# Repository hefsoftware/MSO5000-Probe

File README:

MSO5000 digital probe. 

The schematic was taken almost verbatim from Faeton's digital-probe-rigol-mso5000 (https://oshwlab.com/f33net/digital-probe-rigol-mso5000).
As their work is acknowledged in the original work a special thank goes to people from EEVblog for pinout of the connector.

Changes from Faeton's:
The schematic and PCB were drawn with Kicad.
The single LVDS buffer SN65LVDS1 was replaced with a 4-line buffer SN65LVDS04. 
Changed linear regulator to MCP1825ST-3302E/DB which has a different pinout from original (available on Digikey)
Inputs order was switched from original (now pin 0 is on the left and pin 15 is on the right) to make routing more "natural" and make the board more compact.

TODO: Add option for switching tab from GND to Vin to make use of original regulator MC33375ST-3.3T3G.

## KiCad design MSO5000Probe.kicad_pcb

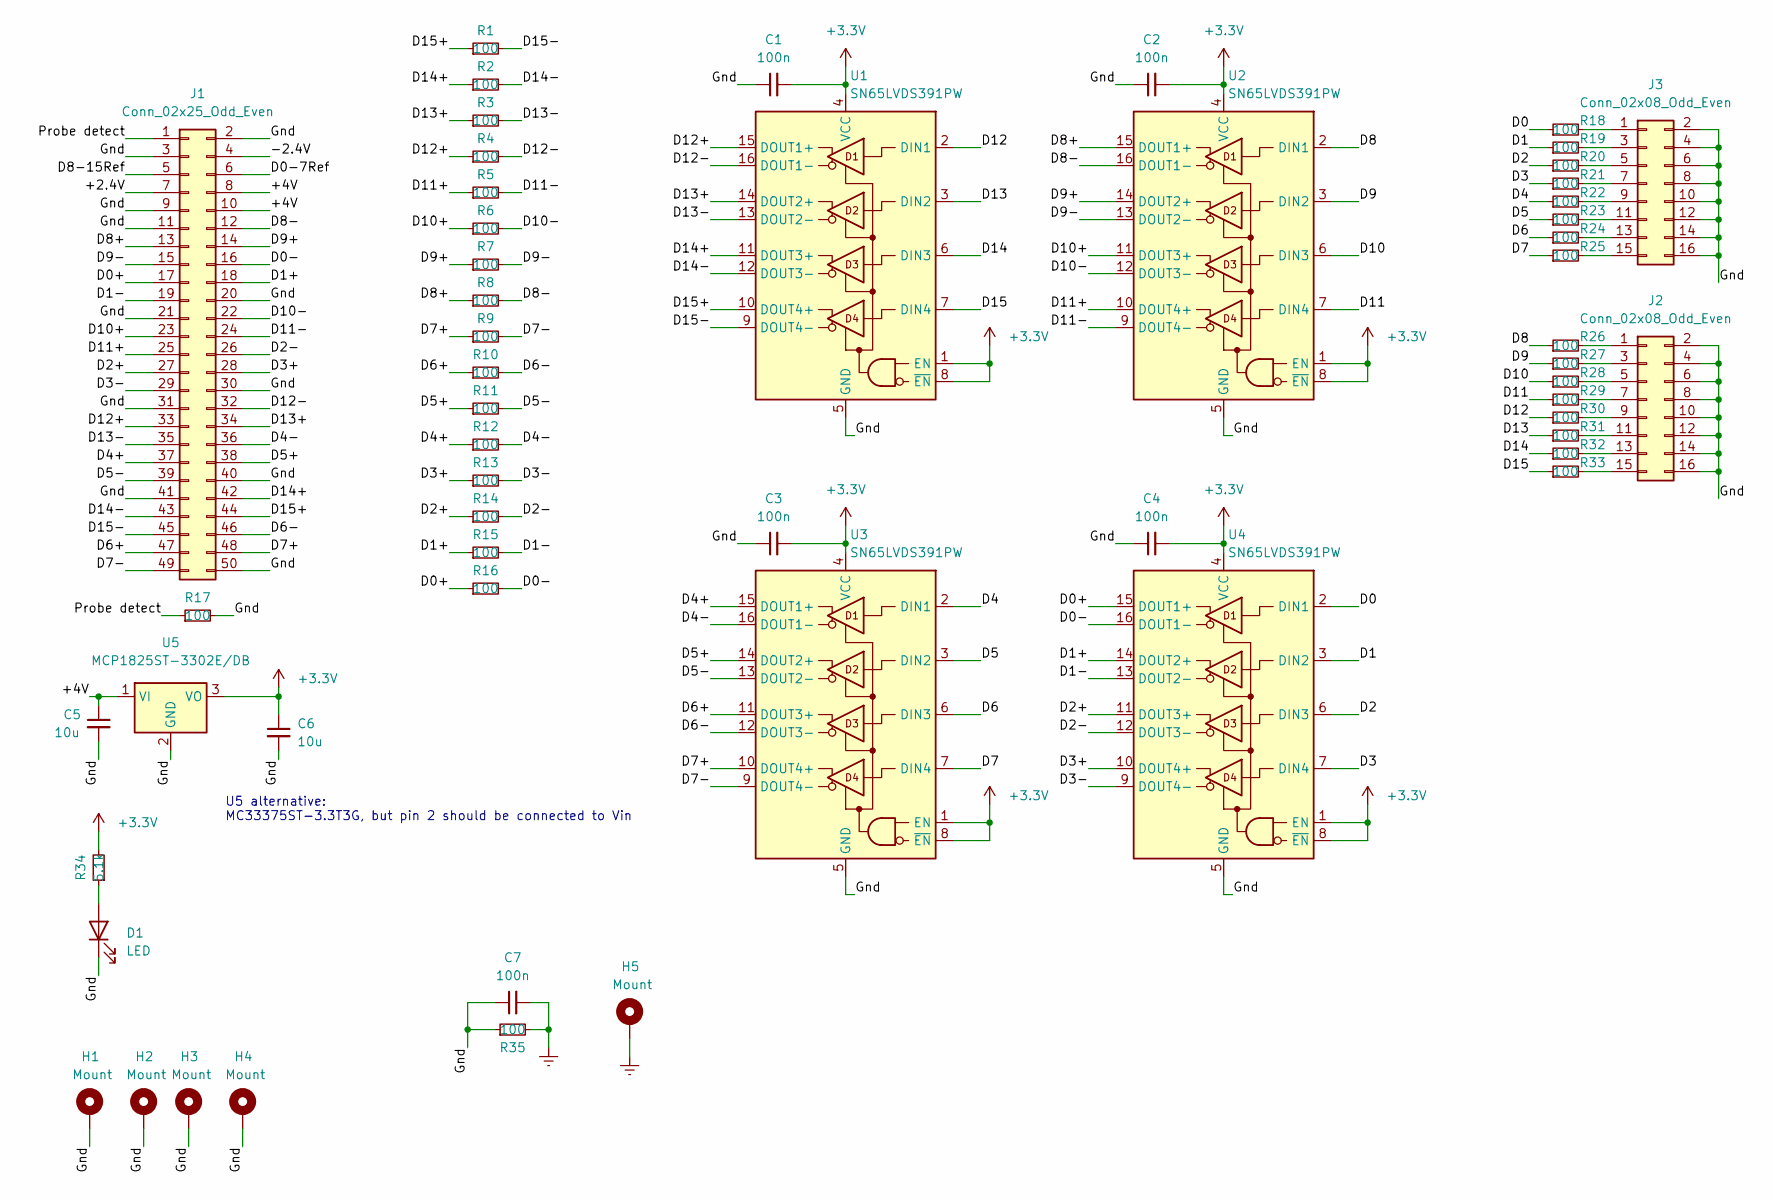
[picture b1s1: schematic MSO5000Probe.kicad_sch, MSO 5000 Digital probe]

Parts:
C1, C2, C3, C4, C7: 100n; C_0805_2012Metric_Pad1.18x1.45mm_HandSolder
C5, C6: 10u; C_0805_2012Metric_Pad1.18x1.45mm_HandSolder
D1: LED; LED_1206_3216Metric_Pad1.42x1.75mm_HandSolder
H1, H2, H3, H4: Mount; MountingHole_2.7mm_Pad_Via
H5: Mount; TestPoint_THTPad_2.5x2.5mm_Drill1.2mm
J1: Conn_02x25_Odd_Even; IDC-Header_2x25_P2.54mm_Vertical
J2, J3: Conn_02x08_Odd_Even; IDC-Header_2x08_P2.54mm_Horizontal
R1, R2, R3, R4, R5, R6, R7, R8, R9, R10, R11, R12, R13, R14, R15, R16, R17, R18, R19, R20, R21, R22, R23, R24, R25, R26, R27, R28, R29, R30, R31, R32, R33, R35: 100; R_0805_2012Metric_Pad1.20x1.40mm_HandSolder
R34: 5.1k; R_0805_2012Metric_Pad1.20x1.40mm_HandSolder
U1, U2, U3, U4: SN65LVDS391PW; TSSOP-16_4.4x5mm_P0.65mm
U5: MCP1825ST-3302E/DB; SOT-223-3_TabPin2

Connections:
+3V3: C1.2, C2.2, C3.2, C4.2, C6.1, R34.2, U1.1 (EN), U1.4 (VCC), U1.8 (~EN), U2.1 (EN), U2.4 (VCC), U2.8 (~EN), U3.1 (EN), U3.4 (VCC), U3.8 (~EN), U4.1 (EN), U4.4 (VCC), U4.8 (~EN), U5.3 (VO)
/+2.4V: J1.7
/+4V: C5.1, J1.8, J1.10, U5.1 (VI)
/-2.4V: J1.4
/D0: R18.1, U4.2 (DIN1)
/D0+: J1.17, R16.1, U4.15 (DOUT1+)
/D0-: J1.16, R16.2, U4.16 (DOUT1-)
/D0-7Ref: J1.6
/D1: R19.1, U4.3 (DIN2)
/D1+: J1.18, R15.1, U4.14 (DOUT2+)
/D1-: J1.19, R15.2, U4.13 (DOUT2-)
/D2: R20.1, U4.6 (DIN3)
/D2+: J1.27, R14.1, U4.11 (DOUT3+)
/D2-: J1.26, R14.2, U4.12 (DOUT3-)
/D3: R21.1, U4.7 (DIN4)
/D3+: J1.28, R13.1, U4.10 (DOUT4+)
/D3-: J1.29, R13.2, U4.9 (DOUT4-)
/D4: R22.1, U3.2 (DIN1)
/D4+: J1.37, R12.1, U3.15 (DOUT1+)
/D4-: J1.36, R12.2, U3.16 (DOUT1-)
/D5: R23.1, U3.3 (DIN2)
/D5+: J1.38, R11.1, U3.14 (DOUT2+)
/D5-: J1.39, R11.2, U3.13 (DOUT2-)
/D6: R24.1, U3.6 (DIN3)
/D6+: J1.47, R10.1, U3.11 (DOUT3+)
/D6-: J1.46, R10.2, U3.12 (DOUT3-)
/D7: R25.1, U3.7 (DIN4)
/D7+: J1.48, R9.1, U3.10 (DOUT4+)
/D7-: J1.49, R9.2, U3.9 (DOUT4-)
/D8: R26.1, U2.2 (DIN1)
/D8+: J1.13, R8.1, U2.15 (DOUT1+)
/D8-: J1.12, R8.2, U2.16 (DOUT1-)
/D8-15Ref: J1.5
/D9: R27.1, U2.3 (DIN2)
/D9+: J1.14, R7.1, U2.14 (DOUT2+)
/D9-: J1.15, R7.2, U2.13 (DOUT2-)
/D10: R28.1, U2.6 (DIN3)
/D10+: J1.23, R6.1, U2.11 (DOUT3+)
/D10-: J1.22, R6.2, U2.12 (DOUT3-)
/D11: R29.1, U2.7 (DIN4)
/D11+: J1.25, R5.1, U2.10 (DOUT4+)
/D11-: J1.24, R5.2, U2.9 (DOUT4-)
/D12: R30.1, U1.2 (DIN1)
/D12+: J1.33, R4.1, U1.15 (DOUT1+)
/D12-: J1.32, R4.2, U1.16 (DOUT1-)
/D13: R31.1, U1.3 (DIN2)
/D13+: J1.34, R3.1, U1.14 (DOUT2+)
/D13-: J1.35, R3.2, U1.13 (DOUT2-)
/D14: R32.1, U1.6 (DIN3)
/D14+: J1.42, R2.1, U1.11 (DOUT3+)
/D14-: J1.43, R2.2, U1.12 (DOUT3-)
/D15: R33.1, U1.7 (DIN4)
/D15+: J1.44, R1.1, U1.10 (DOUT4+)
/D15-: J1.45, R1.2, U1.9 (DOUT4-)
/Gnd: C1.1, C2.1, C3.1, C4.1, C5.2, C6.2, C7.1, D1.1 (K), H1.1, H2.1, H3.1, H4.1, J1.2, J1.3, J1.9, J1.11, J1.20, J1.21, J1.30, J1.31, J1.40, J1.41, J1.50, J2.2, J2.4, J2.6, J2.8, J2.10, J2.12, J2.14, J2.16, J3.2, J3.4, J3.6, J3.8, J3.10, J3.12, J3.14, J3.16, R17.2, R35.1, U1.5 (GND), U2.5 (GND), U3.5 (GND), U4.5 (GND), U5.2 (GND)
/Probe detect: J1.1, R17.1
Earth: C7.2, H5.1, R35.2
unnamed: D1.2 (A), R34.1
unnamed: J2.1, R26.2
unnamed: J2.3, R27.2
unnamed: J2.5, R28.2
unnamed: J2.7, R29.2
unnamed: J2.9, R30.2
unnamed: J2.11, R31.2
unnamed: J2.13, R32.2
unnamed: J2.15, R33.2
unnamed: J3.1, R18.2
unnamed: J3.3, R19.2
unnamed: J3.5, R20.2
unnamed: J3.7, R21.2
unnamed: J3.9, R22.2
unnamed: J3.11, R23.2
unnamed: J3.13, R24.2
unnamed: J3.15, R25.2

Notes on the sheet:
U5 alternative: MC33375ST-3.3T3G, but pin 2 should be connected to Vin

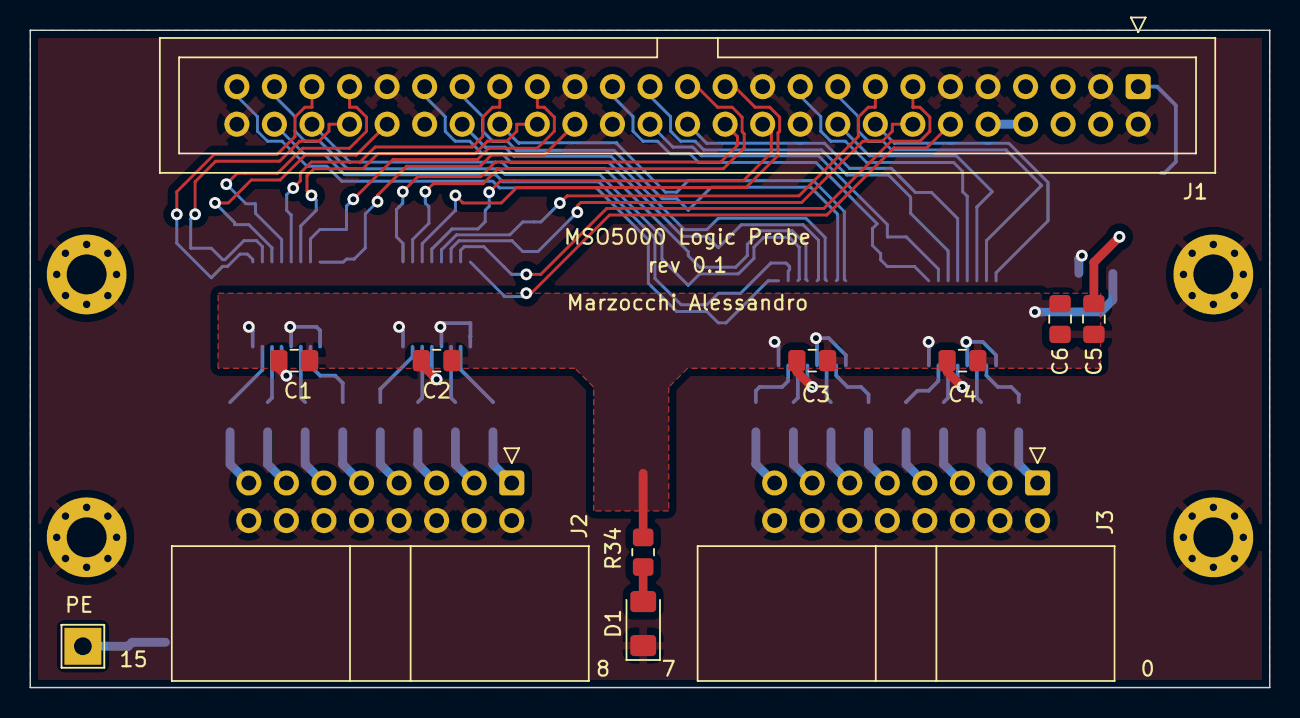
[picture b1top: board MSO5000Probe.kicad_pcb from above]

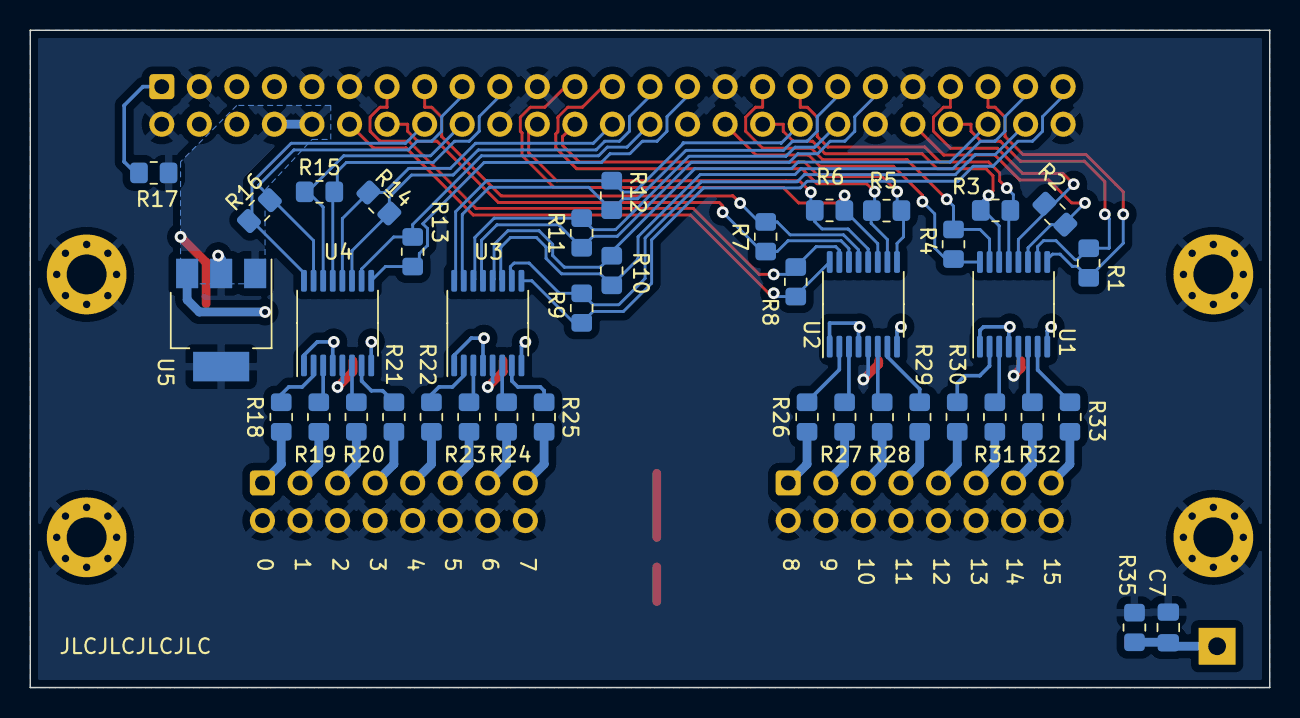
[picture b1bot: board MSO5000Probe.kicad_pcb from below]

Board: 2 copper layers, 83.8 x 44.4 mm, 56 parts (40 on the bottom side), 70 nets.

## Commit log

2022-05-12 Initial release

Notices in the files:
MSO5000Probe.kicad_sch:
Released under GPL 3.0 license
